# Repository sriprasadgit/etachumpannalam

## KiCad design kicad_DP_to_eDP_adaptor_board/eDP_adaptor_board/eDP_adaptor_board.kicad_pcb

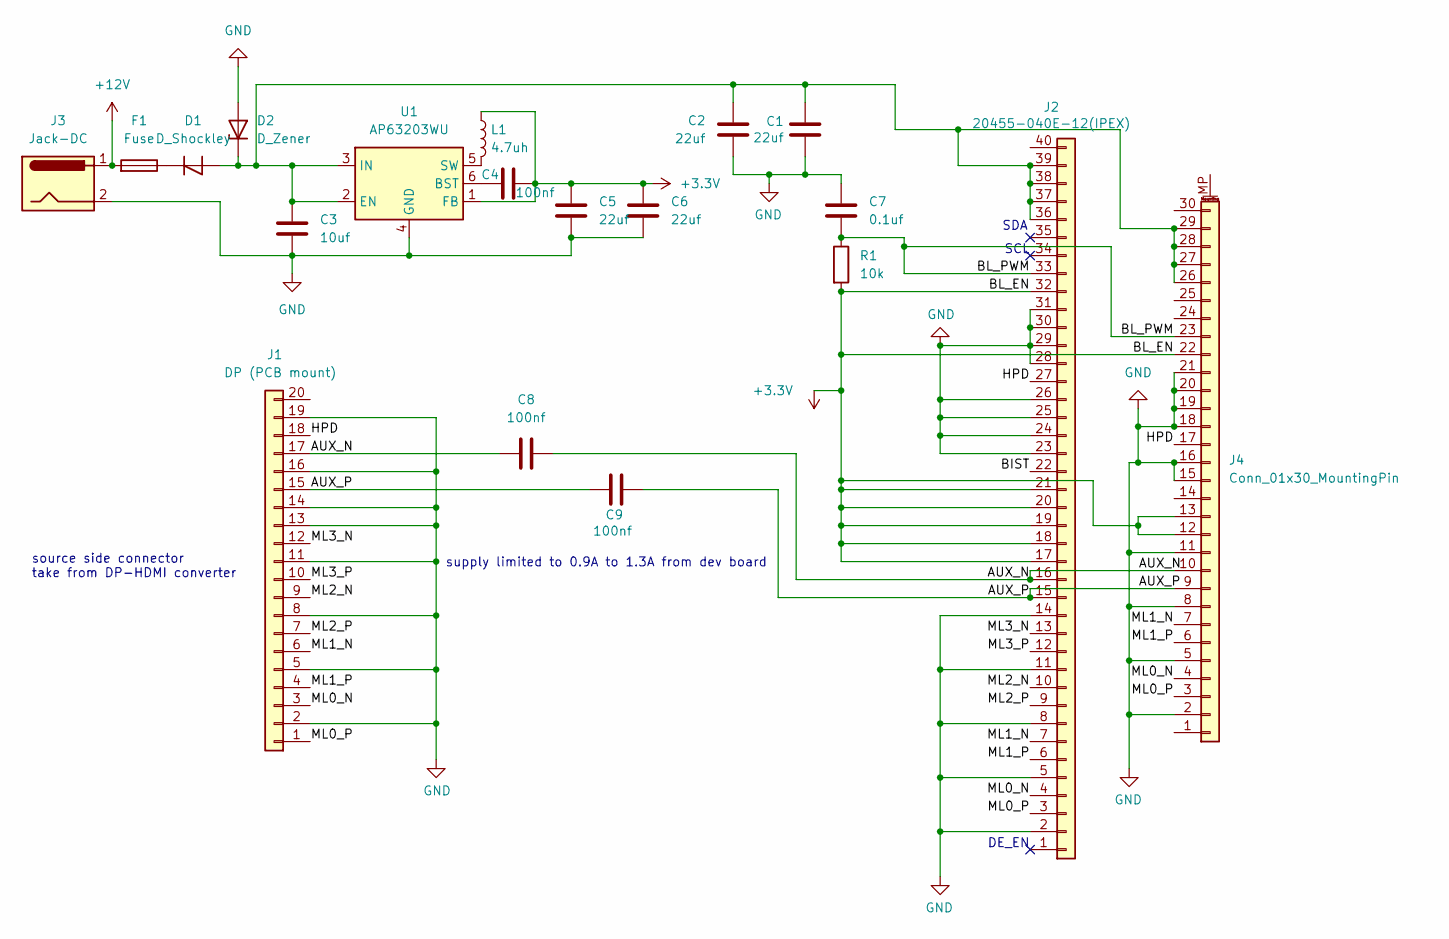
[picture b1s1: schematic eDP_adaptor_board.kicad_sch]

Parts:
C1, C2, C5, C6: 22uf; C_0805_2012Metric
C3: 10uf; C_0805_2012Metric
C4, C8, C9: 100nf; C_0402_1005Metric
C7: 0.1uf; C_0402_1005Metric
D1: D_Shockley; D_SOD-123F
D2: D_Zener; D_SOD-123F
F1: Fuse; Fuse_1206_3216Metric
J1: DP (PCB mount); AMPHENOL_DPF20102721TR
J2: 20455-040E-12(IPEX); IPEX_20455-040E-76
J3: Jack-DC; BarrelJack_CUI_PJ-102AH_Horizontal
J4: Conn_01x30_MountingPin; Hirose_FH12-30S-0.5SH_1x30-1MP_P0.50mm_Horizontal
L1: 4.7uh; L_1210_3225Metric
R1: 10k; R_0805_2012Metric
U1: AP63203WU; TSOT-23-6

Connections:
+3.3V: C4.2, C5.1, C6.1, J2.17, J2.18, J2.19, J2.20, J2.21, J2.32, J4.12, J4.13, J4.22, L1.1, R1.2, U1.1 (FB)
+12V: F1.2, J3.1
/AUX_N: C8.1, C8.2, J1.17, J2.16, J4.10
/AUX_P: C9.1, C9.2, J1.15, J2.15, J4.9
/BIST: J2.22
/BL_PWM: C7.2, J2.33, J4.23, R1.1
/HPD: J1.18, J2.27, J4.17
/ML0_N: J1.3, J2.4, J4.4
/ML0_P: J1.1, J2.3, J4.3
/ML1_N: J1.6, J2.7, J4.7
/ML1_P: J1.4, J2.6, J4.6
/ML2_N: J1.9, J2.10
/ML2_P: J1.7, J2.9
/ML3_N: J1.12, J2.13
/ML3_P: J1.10, J2.12
GND: C1.2, C2.2, C3.2, C5.2, C6.2, C7.1, D2.2 (A), J1.2, J1.5, J1.8, J1.11, J1.13, J1.14, J1.16, J1.19, J1.SH1, J1.SH2, J1.SH3, J1.SH4, J2.2, J2.5, J2.8, J2.11, J2.14, J2.23, J2.24, J2.25, J2.26, J2.28, J2.29, J2.30, J2.31, J3.2, J4.2, J4.5, J4.8, J4.11, J4.15, J4.16, J4.18, J4.19, J4.20, J4.21, J4.MP (MountPin), U1.4 (GND)
unnamed: C1.1, C2.1, C3.1, D1.2 (A), D2.1 (K), J2.36, J2.37, J2.38, J2.39, J4.26, J4.27, J4.28, J4.29, U1.2 (EN), U1.3 (IN)
unnamed: D1.1 (K), F1.1
unnamed: C4.1, U1.6 (BST)
unnamed: L1.2, U1.5 (SW)

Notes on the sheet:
SDA
DE_EN
source side connector take from DP-HDMI converter
supply limited to 0.9A to 1.3A from dev board
SCL

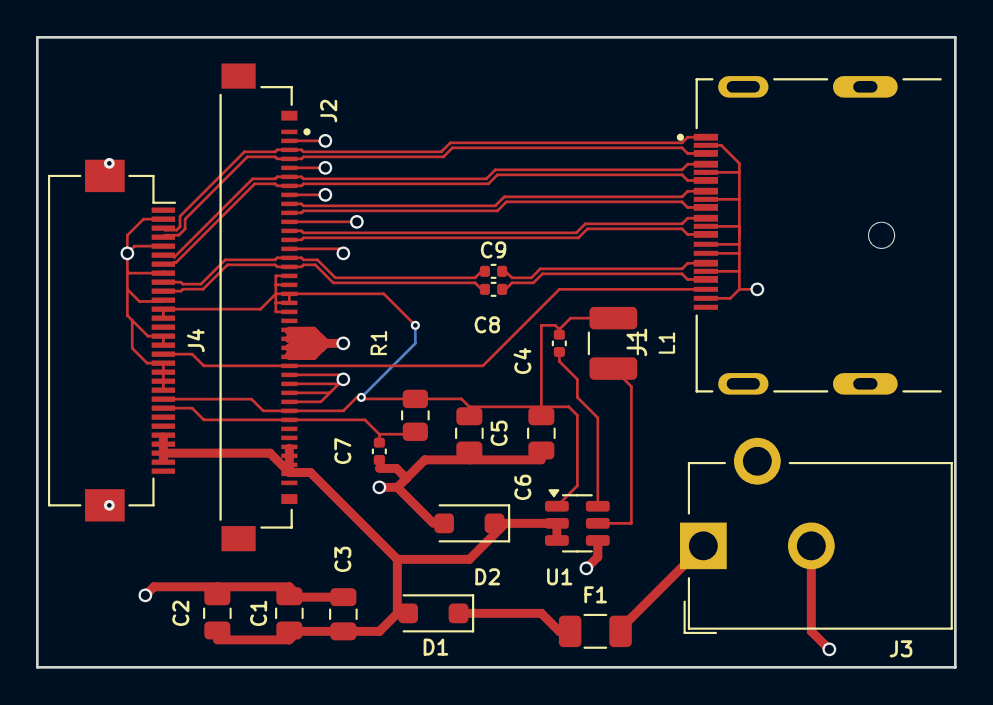
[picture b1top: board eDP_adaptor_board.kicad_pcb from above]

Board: 4 copper layers, 51.0 x 35.0 mm, 19 parts (0 on the bottom side), 19 nets.

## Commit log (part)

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2026-04-17 Add files via upload
    smart desk yaml
2026-06-26 Create esphome_analog_clock
2026-06-26 Create esphome_watch_with_background
2026-06-27 Create esphome_clock_white
